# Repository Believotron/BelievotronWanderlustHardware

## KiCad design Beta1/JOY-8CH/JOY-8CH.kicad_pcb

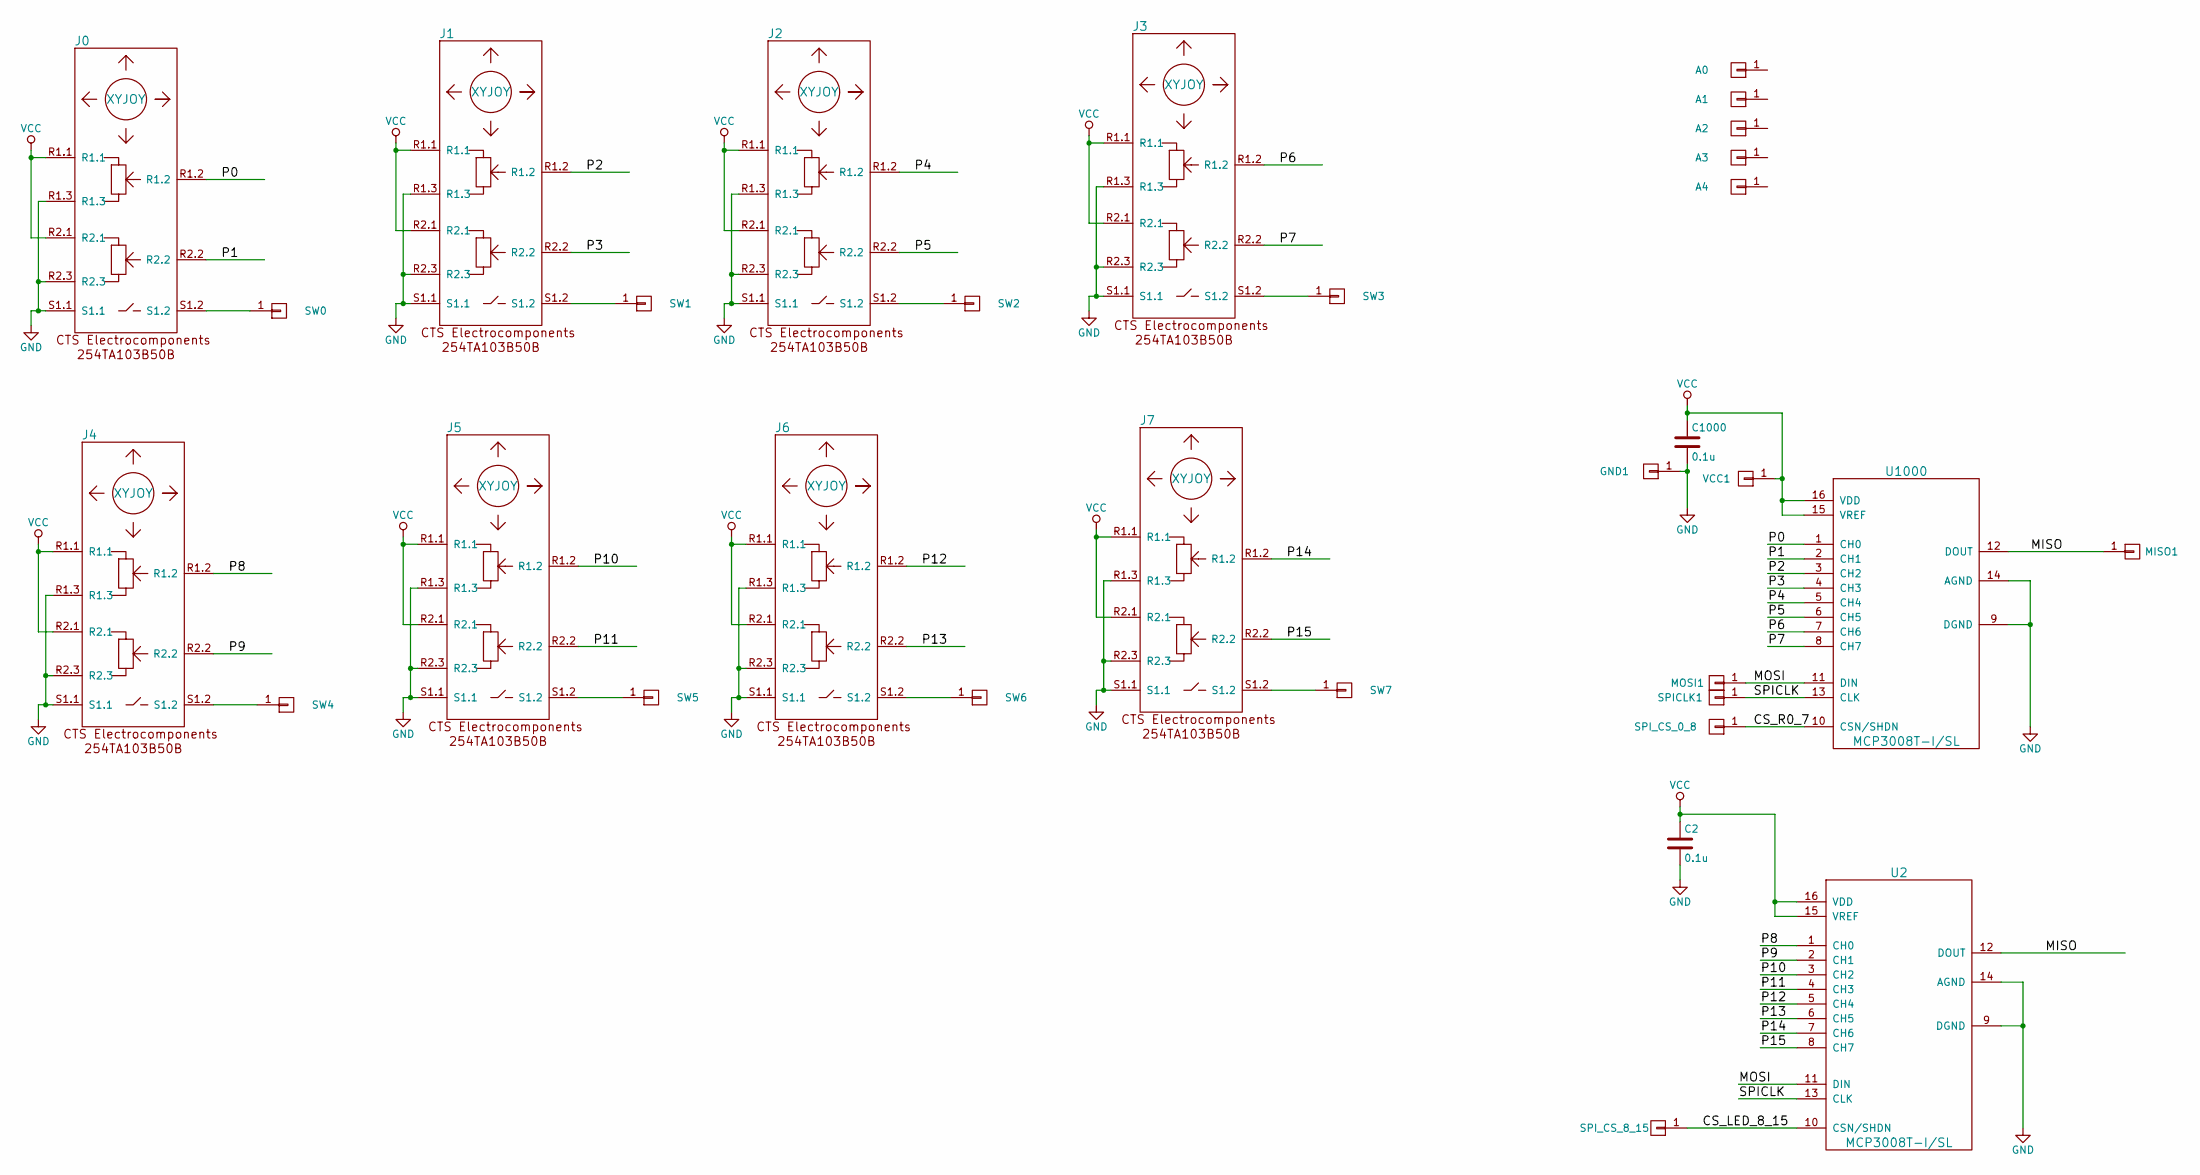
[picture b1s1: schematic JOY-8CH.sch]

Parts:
A0, A1, A2, A3, A4: CONN_01X01; TH_0.1_1x2_Jumper; MPN ON_PCB
C2, C1000: 0.1u; C_0603; MPN CC0603KRX7R9BB104
GND1: CONN_01X01; TH_0.1_1x2_Jumper; MPN ON_PCB
J0, J1, J2, J3, J4, J5, J6, J7: XYJOY; XY_JOY_254TA103B50B
MISO1: CONN_01X01; TH_0.1_1x2_Jumper; MPN ON_PCB
MOSI1: CONN_01X01; TH_0.1_1x2_Jumper; MPN ON_PCB
SPICLK1: CONN_01X01; TH_0.1_1x2_Jumper; MPN ON_PCB
SPI_CS_0_8, SPI_CS_8_15: CONN_01X01; TH_0.1_1x2_Jumper; MPN ON_PCB
SW0, SW1, SW2, SW3, SW4, SW5, SW6, SW7: CONN_01X01; TH_0.1_1x2_Jumper; MPN ON_PCB
U2, U1000: MCP3008T-I/SL; SOIC-16; MPN MCP3008T-I/SL
VCC1: CONN_01X01; TH_0.1_1x2_Jumper; MPN ON_PCB

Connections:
/CS_LED_8_15: SPI_CS_8_15.1, U2.10 (CSN/SHDN)
/CS_R0_7: SPI_CS_0_8.1, U1000.10 (CSN/SHDN)
/MISO: MISO1.1, U2.12 (DOUT), U1000.12 (DOUT)
/MOSI: MOSI1.1, U2.11 (DIN), U1000.11 (DIN)
/P0: J0.R1.2, U1000.1 (CH0)
/P1: J0.R2.2, U1000.2 (CH1)
/P2: J1.R1.2, U1000.3 (CH2)
/P3: J1.R2.2, U1000.4 (CH3)
/P4: J2.R1.2, U1000.5 (CH4)
/P5: J2.R2.2, U1000.6 (CH5)
/P6: J3.R1.2, U1000.7 (CH6)
/P7: J3.R2.2, U1000.8 (CH7)
/P8: J4.R1.2, U2.1 (CH0)
/P9: J4.R2.2, U2.2 (CH1)
/P10: J5.R1.2, U2.3 (CH2)
/P11: J5.R2.2, U2.4 (CH3)
/P12: J6.R1.2, U2.5 (CH4)
/P13: J6.R2.2, U2.6 (CH5)
/P14: J7.R1.2, U2.7 (CH6)
/P15: J7.R2.2, U2.8 (CH7)
/SPICLK: SPICLK1.1, U2.13 (CLK), U1000.13 (CLK)
GND: C2.2, C1000.2, GND1.1, J0.R1.3, J0.R2.3, J0.S1.1, J1.R1.3, J1.R2.3, J1.S1.1, J2.R1.3, J2.R2.3, J2.S1.1, J3.R1.3, J3.R2.3, J3.S1.1, J4.R1.3, J4.R2.3, J4.S1.1, J5.R1.3, J5.R2.3, J5.S1.1, J6.R1.3, J6.R2.3, J6.S1.1, J7.R1.3, J7.R2.3, J7.S1.1, U2.9 (DGND), U2.14 (AGND), U1000.9 (DGND), U1000.14 (AGND)
unnamed: J0.S1.2, SW0.1
unnamed: J1.S1.2, SW1.1
unnamed: J2.S1.2, SW2.1
unnamed: J3.S1.2, SW3.1
unnamed: J4.S1.2, SW4.1
unnamed: J5.S1.2, SW5.1
unnamed: J6.S1.2, SW6.1
unnamed: J7.S1.2, SW7.1
VCC: C2.1, C1000.1, J0.R1.1, J0.R2.1, J1.R1.1, J1.R2.1, J2.R1.1, J2.R2.1, J3.R1.1, J3.R2.1, J4.R1.1, J4.R2.1, J5.R1.1, J5.R2.1, J6.R1.1, J6.R2.1, J7.R1.1, J7.R2.1, U2.15 (VREF), U2.16 (VDD), U1000.15 (VREF), U1000.16 (VDD), VCC1.1

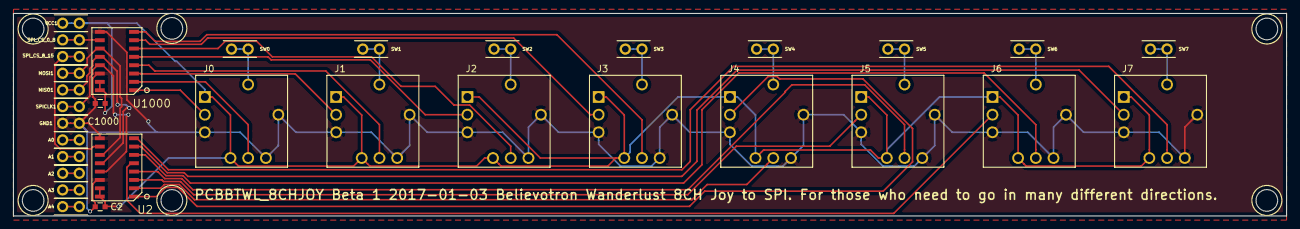
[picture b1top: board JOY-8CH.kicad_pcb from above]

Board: 2 copper layers, 194.0 x 30.9 mm, 32 parts (0 on the bottom side), 31 nets.

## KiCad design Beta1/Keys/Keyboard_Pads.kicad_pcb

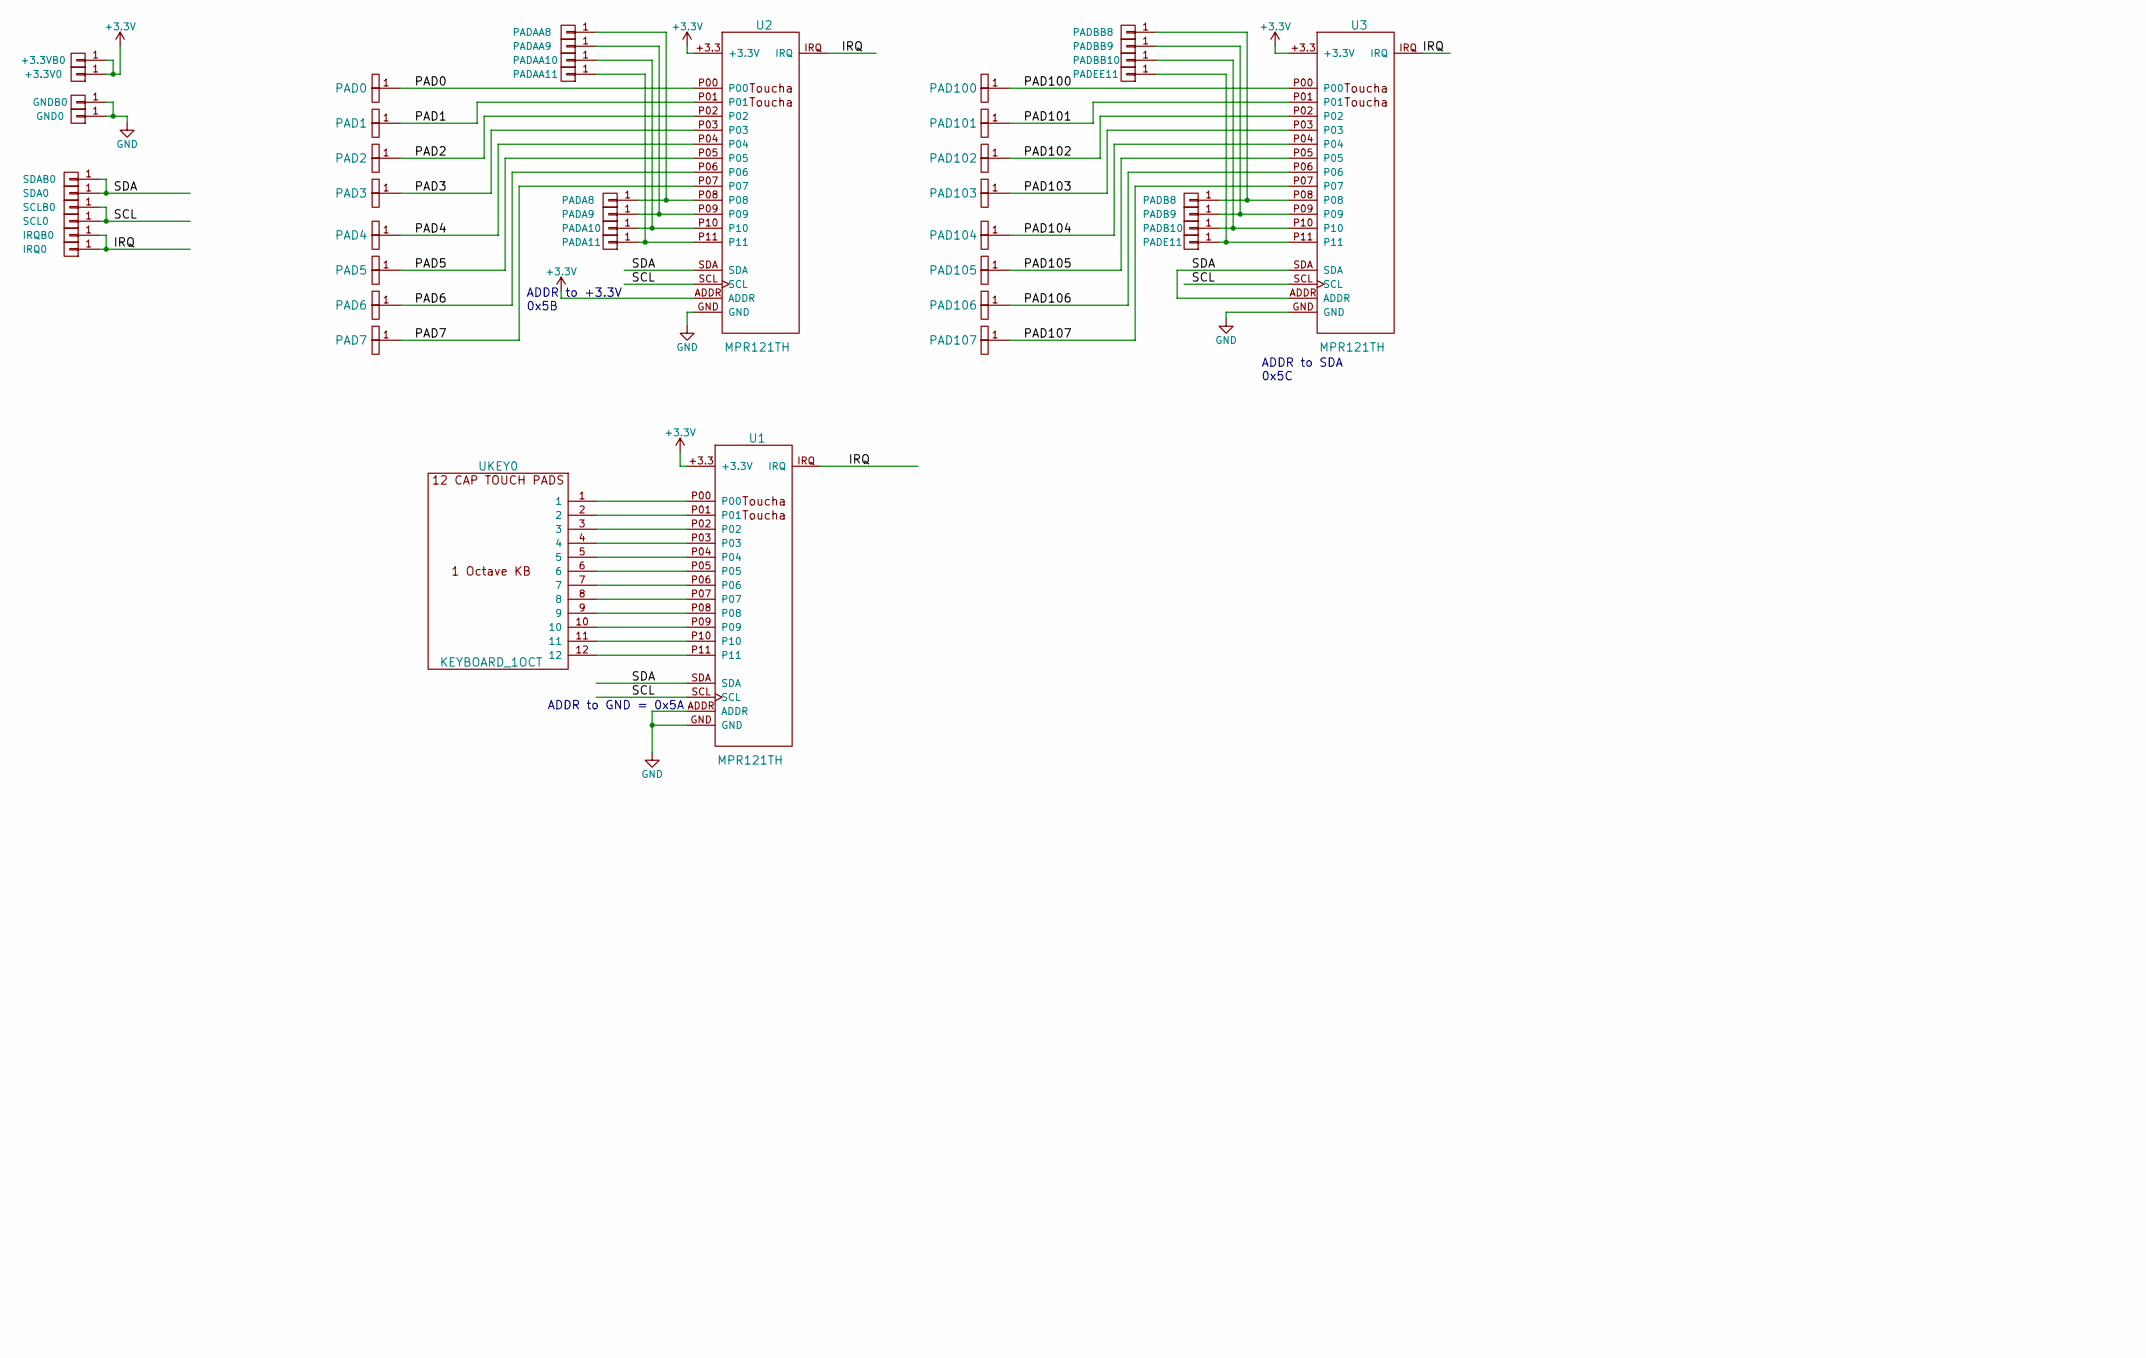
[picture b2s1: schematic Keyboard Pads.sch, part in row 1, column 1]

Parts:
+3.3V0, +3.3VB0: CONN_01X01; single_0.1; MPN ON_PCB
GND0: CONN_01X01; single_0.1; MPN ON_PCB
GNDB0: CONN_01X01; single_0.1; MPN ON_PCB
IRQ0: CONN_01X01; single_0.1; MPN ON_PCB
IRQB0: CONN_01X01; single_0.1; MPN ON_PCB
PAD0, PAD1, PAD2, PAD3, PAD4, PAD5, PAD6, PAD7, PAD100, PAD101, PAD102, PAD103, PAD104, PAD105, PAD106, PAD107: TOUCHPAD_10CM; TOUCH_PAD_10CM
PADA8, PADA9, PADA10, PADA11: CONN_01X01; single_0.1; MPN ON_PCB
PADAA8, PADAA9, PADAA10, PADAA11: CONN_01X01; single_0.1; MPN ON_PCB
PADB8, PADB9, PADB10: CONN_01X01; single_0.1; MPN ON_PCB
PADBB8, PADBB9, PADBB10: CONN_01X01; single_0.1; MPN ON_PCB
PADE11: CONN_01X01; single_0.1; MPN ON_PCB
PADEE11: CONN_01X01; single_0.1; MPN ON_PCB
SCL0: CONN_01X01; single_0.1; MPN ON_PCB
SCLB0: CONN_01X01; single_0.1; MPN ON_PCB
SDA0: CONN_01X01; single_0.1; MPN ON_PCB
SDAB0: CONN_01X01; single_0.1; MPN ON_PCB
U1, U2, U3: MPR121TH; MPN BTWLMPR121TH
UKEY0: KEYBOARD_1OCT; Keyboard_1_Octave_20CM; MPN PCB

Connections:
+3V3: +3.3V0.1, +3.3VB0.1, U1.+3.3 (+3.3V), U2.+3.3 (+3.3V), U2.ADDR, U3.+3.3 (+3.3V)
/IRQ: IRQ0.1, IRQB0.1, U1.IRQ, U2.IRQ, U3.IRQ
/PAD0: PAD0.1, U2.P00
/PAD1: PAD1.1, U2.P01
/PAD2: PAD2.1, U2.P02
/PAD3: PAD3.1, U2.P03
/PAD4: PAD4.1, U2.P04
/PAD5: PAD5.1, U2.P05
/PAD6: PAD6.1, U2.P06
/PAD7: PAD7.1, U2.P07
/PAD100: PAD100.1, U3.P00
/PAD101: PAD101.1, U3.P01
/PAD102: PAD102.1, U3.P02
/PAD103: PAD103.1, U3.P03
/PAD104: PAD104.1, U3.P04
/PAD105: PAD105.1, U3.P05
/PAD106: PAD106.1, U3.P06
/PAD107: PAD107.1, U3.P07
/SCL: SCL0.1, SCLB0.1, U1.SCL, U2.SCL, U3.SCL
/SDA: SDA0.1, SDAB0.1, U1.SDA, U2.SDA, U3.ADDR, U3.SDA
GND: GND0.1, GNDB0.1, U1.ADDR, U1.GND, U2.GND, U3.GND
unnamed: PADA8.1, PADAA8.1, U2.P08
unnamed: PADA9.1, PADAA9.1, U2.P09
unnamed: PADA10.1, PADAA10.1, U2.P10
unnamed: PADA11.1, PADAA11.1, U2.P11
unnamed: PADB8.1, PADBB8.1, U3.P08
unnamed: PADB9.1, PADBB9.1, U3.P09
unnamed: PADB10.1, PADBB10.1, U3.P10
unnamed: PADE11.1, PADEE11.1, U3.P11
unnamed: U1.P00, UKEY0.1
unnamed: U1.P01, UKEY0.2
unnamed: U1.P02, UKEY0.3
unnamed: U1.P03, UKEY0.4
unnamed: U1.P04, UKEY0.5
unnamed: U1.P05, UKEY0.6
unnamed: U1.P06, UKEY0.7
unnamed: U1.P07, UKEY0.8
unnamed: U1.P08, UKEY0.9
unnamed: U1.P09, UKEY0.10
unnamed: U1.P10, UKEY0.11
unnamed: U1.P11, UKEY0.12

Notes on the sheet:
LED strip, APA102C x 8, + 0.1" TH for debug / separation
ADDR to GND = 0x5A
ADDR to +3.3V 0x5B
ADDR to SDA 0x5C

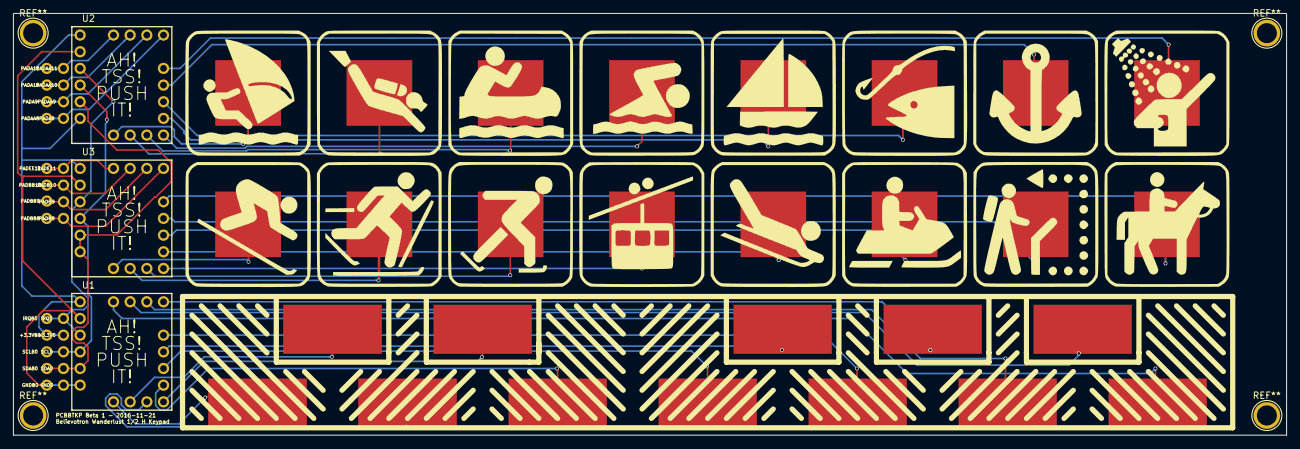
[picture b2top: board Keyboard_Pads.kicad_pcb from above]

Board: 2 copper layers, 194.0 x 64.2 mm, 46 parts (0 on the bottom side), 41 nets.

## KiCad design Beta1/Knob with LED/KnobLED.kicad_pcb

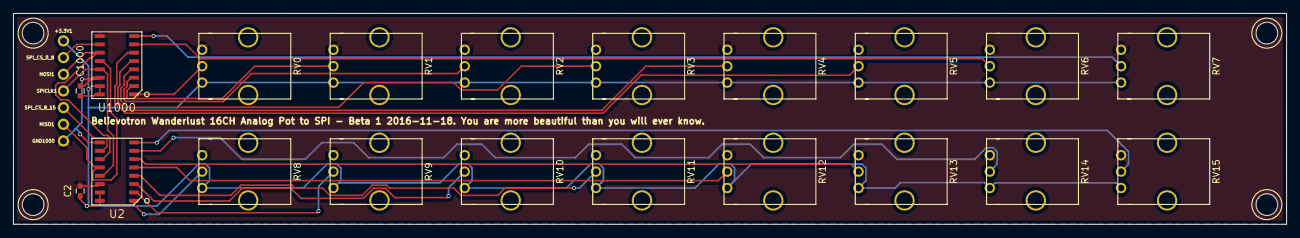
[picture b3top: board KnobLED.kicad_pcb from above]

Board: 2 copper layers, 194.0 x 32.1 mm, 27 parts (0 on the bottom side), 23 nets.

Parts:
+3.3V1: CONN_01X01; single_0.1
C2, C1000: 0.1u; C_0603
GND1000: CONN_01X01; single_0.1
MISO1: CONN_01X01; single_0.1
MOSI1: CONN_01X01; single_0.1
RV0, RV1, RV2, RV3, RV4, RV5, RV6, RV7, RV8, RV9, RV10, RV11, RV12, RV13, RV14, RV15: POT; RV09AF-40-20K-B10K
SPICLK1: CONN_01X01; single_0.1
SPI_CS_0_8, SPI_CS_8_15: CONN_01X01; single_0.1
U2, U1000: MCP3008T-I/SL; SOIC-16

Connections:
+3V3: +3.3V1.1, C2.1, C1000.1, RV0.1, RV1.1, RV2.1, RV3.1, RV4.1, RV5.1, RV6.1, RV7.1, RV8.1, RV9.1, RV10.1, RV11.1, RV12.1, RV13.1, RV14.1, RV15.1, U2.15, U2.16, U1000.15, U1000.16
/Knobs/CS_LED_8_15: SPI_CS_8_15.1, U2.10
/Knobs/CS_R0_7: SPI_CS_0_8.1, U1000.10
/Knobs/MISO: MISO1.1, U2.12, U1000.12
/Knobs/MOSI: MOSI1.1, U2.11, U1000.11
/Knobs/P0: RV0.2, U1000.1
/Knobs/P1: RV1.2, U1000.2
/Knobs/P2: RV2.2, U1000.3
/Knobs/P3: RV3.2, U1000.4
/Knobs/P4: RV4.2, U1000.5
/Knobs/P5: RV5.2, U1000.6
/Knobs/P6: RV6.2, U1000.7
/Knobs/P7: RV7.2, U1000.8
/Knobs/P8: RV8.2, U2.1
/Knobs/P9: RV9.2, U2.2
/Knobs/P10: RV10.2, U2.3
/Knobs/P11: RV11.2, U2.4
/Knobs/P12: RV12.2, U2.5
/Knobs/P13: RV13.2, U2.6
/Knobs/P14: RV14.2, U2.7
/Knobs/P15: RV15.2, U2.8
/Knobs/SPICLK: SPICLK1.1, U2.13, U1000.13
GND: C2.2, C1000.2, GND1000.1, RV0.3, RV1.3, RV2.3, RV3.3, RV4.3, RV5.3, RV6.3, RV7.3, RV8.3, RV9.3, RV10.3, RV11.3, RV12.3, RV13.3, RV14.3, RV15.3, U2.9, U2.14, U1000.9, U1000.14
